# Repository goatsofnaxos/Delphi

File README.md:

# Delphi

Delphi workflow

### Acquisition Prerequisites

The following need to be installed once on a fresh new system in order to bootstrap the Bonsai environment correctly (always check after each download that it has been completed):

 * Windows 10 or greater (Windows 11 after 9/2025)
 * [Visual Studio Code](https://code.visualstudio.com/) (recommended for editing code scripts and git commits)
 * [.NET 8.0 SDK](https://dotnet.microsoft.com/en-us/download/dotnet/8.0)
 * [.NET Framework 4.7.2 Developer Pack](https://dotnet.microsoft.com/download/dotnet-framework/thank-you/net472-developer-pack-offline-installer) (required for intellisense when editing code scripts)
 * [Git for Windows](https://gitforwindows.org/) (recommended for cloning and manipulating this repository)
 * [Visual C++ Redistributable for Visual Studio 2012](https://www.microsoft.com/en-us/download/details.aspx?id=30679) (native dependency for OpenCV)
 * [FTDI D2XX COM Port Driver 2.12.28](https://ftdichip.com/drivers/d2xx-drivers/) (serial port drivers for HARP devices)
   * To download the installer, scroll down, and click *available as a setup executable*.
 * [Spinnaker SDK 1.29.0.5](https://www.flir.co.uk/support/products/spinnaker-sdk/#Downloads) (device drivers for FLIR cameras, sign in required, look in the archived stable versions for 1.29.0.5 64-bit full install)
 * [Github Desktop](https://desktop.github.com/download/) (convenient for testing different PRs)
 * [Python](https://www.python.org/downloads/)

 ### Setting up the Bonsai environment
 To set up a Bonsai environment for running Delphi, use the terminal to clone the repo into a local folder:

 ``` 
 git clone https://github.com/goatsofnaxos/Delphi.git 
 ```

 Now navigate into Delphi/.bonsai and run the `Setup.ps1` script (on Windows right-click > Run with powershell). Once all dependencies have been restored Bonsai can be launched in a local environment from the `.exe` in this folder.

 ### Setting up the Python environment
 A local Python environment is used within the Delphi workflow for certain subprocesses (e.g. robocopy of data). This is separate to the Python environment used for postprocessing and data analysis. To activate this environment after cloning the repo, navigate to Delphi/.python and run the `setup.ps1` script (on Windows right-click > Run with powershell).

 ### Session Settings
 Experiment parameters are based on two data schemas `data-schema` and `rule-schema`. `data-schema` defines global experiment parameters such as animal ID information, logging paths, odor delivery times etc. `rule-schema` defines the experiment state machine with rules for how different states transition to each other. Implementations of these schemas are defined in `.yml` files provided by the user that are then loaded in Bonsai to set up experiment parameters.

 #### Working with data schemas in Visual Studio Code
 To create and edit schema implementations with full autcomplete and hinting, Visual Studio Code requires some extensions to be added:
 * json (ZainChen.json)
 * JSON Schema Validator (tberman.json-schema-validator)
 * YAML (redhat.vscode-yaml)

 #### Creating an experiment parameter file
 To create an experiment parameter file based on the `data-schema`, create a new `.yml` file and add a reference to the `data-schema` at the top of the file:

 ```
 %YAML 1.1
 ---
 # yaml-language-server: $schema=data-schema.json
 ```

The `data-schema` has three main groups of parameters to define: general metadata; camera properties; and line mappings, e.g.:

```
metadata:
  animalId: CK001
  loggingRootPath: C:\Users\user\data\
  chargeTime: 0.2
  minimumPokeTime: 0.1
  maximumPokeTime: 10
  robocopyTimeInterval: 3600
  showHarpLeds: false
  maxVideoLength: 20
  minOdorDelivery: 0.1
  maxOdorDelivery: 8
  switchTime1: 0.035
  switchTime2: 0.025
  useVacuum: true
  *There are more parameters to set now. Refer to "Checklist_HIW3_2024_updated....docx" file in
   Delphi > Design and Operations > Running the experiment

cameraProperties:
  imagingRate: 100
  preEventBufferFrames: 20
  postEventBufferFrames: 20
  bufferInterval: 1

lineMappings:
  odorMap:
    -   {name: "OdorA", line: 5}
    -   {name: "OdorB", line: 6}
    -   {name: "OdorC", line: 7}
  portLine: 0
  vacuumLine: 2
  auxLine: 1
```

#### Creating a rule file
To create a rule file based on the `rule-schema`, create a new `.yml` file and add a reference to the `rule-schema` at the top of the file.

```
%YAML 1.1
---
# yaml-language-server: $schema=rule-schema.json
```

Rule files have two main components:
* The rule alias which defines the human-readable name or description of the rule.
* State transition definitions which define which state to transition to after a given state has completed. The state names given here must match their names in the Bonsai workflow. For example:

```
ruleAlias: Rule1

stateDefinitions:
  -   {name: "OdorA", transitionsTo: "OdorB"}
  -   {name: "OdorB", transitionsTo: "OdorC"}
  -   {name: "OdorC", transitionsTo: "OdorA"}
  -   {name: "DefaultState", transitionsTo: "OdorA"}
```

It is important to always define a DefaultState transition rule, as this is the default fallback in case any states are not present.

### Running an experiment
To run an experiment, run the Bonsai application from the local environment and open DelphiMain.bonsai. Use the property grid to select the desired experiment parameter file and starting rule file. If the rule file is changed while the experiment is running, Bonsai will attempt to find a transition from its current state in the new rule file. If no transition is defined for that state in the new rule, or any of the states no longer exist in the new rule - Bonsai will transition to the default state.

### Data transfer
The main Delphi workflow periodically copies logged data with [Robocopy](https://learn.microsoft.com/en-us/windows-server/administration/windows-commands/robocopy) to a new data location (can be a local or remote destination). The parameters for this transfer are set via the schema .yml:
  - `loggingRootPath`: where data is immediately logged
  - `remoteTransferRootPath`: where data should be transferred
  - `robocopyTimeInterval`: the time interval (in seconds) that Robocopy should be activated.

Note also that exiting the workflow process with the exit trigger key will initiate Robocopy.

### Analysis Prerequisites

The following need to be installed once on a fresh new system in order to analyze data acquired with Delphi:

 * [Visual Studio Code](https://code.visualstudio.com/) (recommended for editing code scripts and git commits)
 * A Conda distribution such as [Miniconda](https://docs.anaconda.com/free/miniconda/index.html)
 * [Python Extension for VS Code](https://marketplace.visualstudio.com/items?itemName=ms-python.python)
   * This extension needs to be made aware of the Conda installation. To do so, navigate to the extension settings. Under the section **Python: Conda Path**, enter the full path to the conda.bat executable. ([more info](https://stackoverflow.com/a/77615160/3312269).)
 * [Jupyter Extension for VS Code](https://marketplace.visualstudio.com/items?itemName=ms-toolsai.jupyter)

#### Create local Environment

 1. Open the Delphi folder in VS Code
 2. `Ctrl+Shift+P` in VS Code > Python: Create Environment
   * Select Conda
   * Select Python 3.11 kernel
 3. Ensure pip is upgraded by typying this into VSCode terminal:
    ```
    pip install --upgrade pip
    ```
 4. From the VSCode terminal run `pip install -r requirements.txt`
 5. Clone aeon_mecha into a separate directory 
    ```
    git clone https://github.com/SainsburyWellcomeCentre/aeon_mecha.git 
    ```
 6. From the VS Code terminal, `cd` into the aeon_mecha directory and run:
    ```
    python -m pip install -e .
    ```
 7. In VS Code open an analysis notebook (.ipynb) and click "Select kernel" > Python Environments
   * Select .conda local environment
 8. Analysis notebooks should now be able to run. If you get an error saying a module can't be found, try restarting the kernel in the notebook editor.

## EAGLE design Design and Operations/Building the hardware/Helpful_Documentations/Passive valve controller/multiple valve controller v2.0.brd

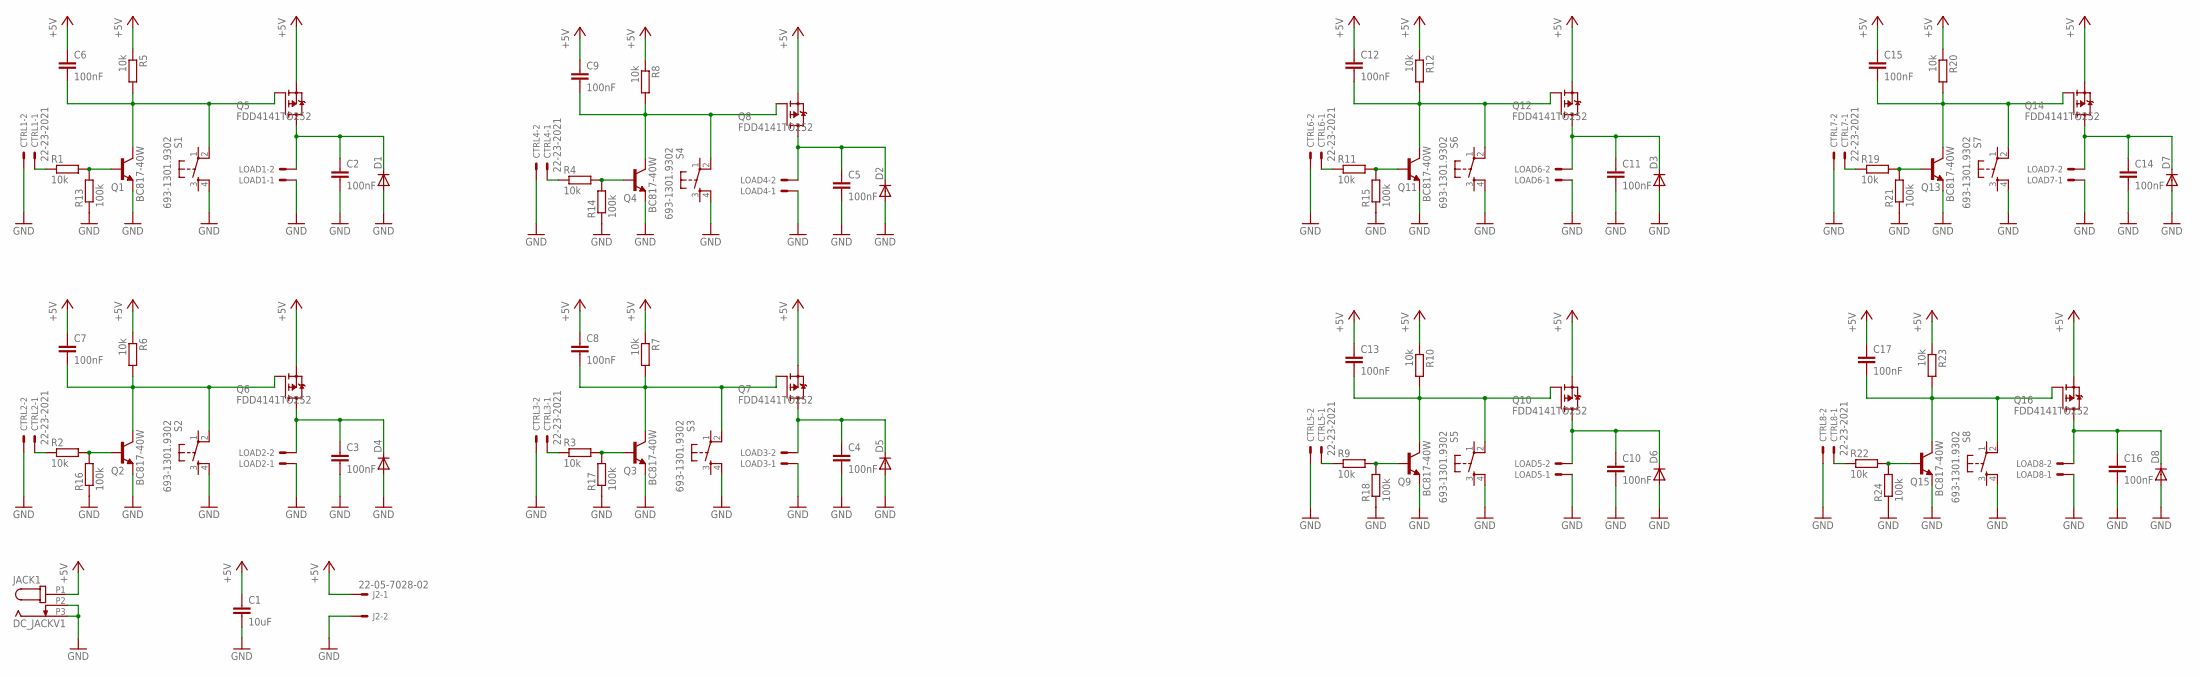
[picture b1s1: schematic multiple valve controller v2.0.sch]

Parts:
C1: 10uF; C1210
C2, C3, C4, C5, C10, C11, C14, C16: 100nF; C1210
C6, C7, C8, C9, C12, C13, C15, C17: 100nF; C0603
CTRL1, CTRL2, CTRL3, CTRL4, CTRL5, CTRL6, CTRL7, CTRL8: 22-23-2021
D1, D2, D3, D4, D5, D6, D7, D8: DIODE-SOD323-R; SOD323-R
J2: 22-05-7028-02; 7395-02
JACK1: DC_JACKV1; DC_POWER_INPUT
LOAD1, LOAD2, LOAD3, LOAD4, LOAD5, LOAD6, LOAD7, LOAD8: 22-23-2021
Q1, Q2, Q3, Q4, Q9, Q11, Q13, Q15: BC817-40W; SOT323-BEC
Q5, Q6, Q7, Q8, Q10, Q12, Q14, Q16: FDD4141TO252; TO252
R1, R2, R3, R4, R9, R11, R19, R22: 10k; R0402
R5, R6, R7, R8, R10, R12, R20, R23: 10k; R0603
R13, R14, R15, R16, R17, R18, R21, R24: 100k; R0402
S1, S2, S3, S4, S5, S6, S7, S8: 693-1301.9302; TACTILE-PTH

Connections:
+5V: C1.1, C6.1, C7.1, C8.1, C9.1, C12.1, C13.1, C15.1, C17.1, J2.1, JACK1.P1 (1), Q5.2 (S), Q6.2 (S), Q7.2 (S), Q8.2 (S), Q10.2 (S), Q12.2 (S), Q14.2 (S), Q16.2 (S), R5.1, R6.1, R7.1, R8.1, R10.1, R12.1, R20.1, R23.1
GND: C1.2, C2.2, C3.2, C4.2, C5.2, C10.2, C11.2, C14.2, C16.2, CTRL1.2, CTRL2.2, CTRL3.2, CTRL4.2, CTRL5.2, CTRL6.2, CTRL7.2, CTRL8.2, D1.A, D2.A, D3.A, D4.A, D5.A, D6.A, D7.A, D8.A, J2.2, JACK1.P2 (2), JACK1.P3 (3), LOAD1.1, LOAD2.1, LOAD3.1, LOAD4.1, LOAD5.1, LOAD6.1, LOAD7.1, LOAD8.1, Q1.E, Q2.E, Q3.E, Q4.E, Q9.E, Q11.E, Q13.E, Q15.E, R13.1, R14.1, R15.1, R16.1, R17.1, R18.1, R21.1, R24.1, S1.4, S2.4, S3.4, S4.4, S5.4, S6.4, S7.4, S8.4
unnamed: CTRL1.1, R1.1
unnamed: C3.1, D4.C, LOAD2.2, Q6.3 (D)
unnamed: C8.2, Q3.C, Q7.1 (G), R7.2, S3.2
unnamed: Q2.B, R2.2, R16.2
unnamed: CTRL2.1, R2.1
unnamed: C4.1, D5.C, LOAD3.2, Q7.3 (D)
unnamed: C13.2, Q9.C, Q10.1 (G), R10.2, S5.2
unnamed: Q3.B, R3.2, R17.2
unnamed: C2.1, D1.C, LOAD1.2, Q5.3 (D)
unnamed: CTRL3.1, R3.1
unnamed: C5.1, D2.C, LOAD4.2, Q8.3 (D)
unnamed: C12.2, Q11.C, Q12.1 (G), R12.2, S6.2
unnamed: Q4.B, R4.2, R14.2
unnamed: CTRL4.1, R4.1
unnamed: C7.2, Q2.C, Q6.1 (G), R6.2, S2.2
unnamed: C9.2, Q4.C, Q8.1 (G), R8.2, S4.2
unnamed: Q1.B, R1.2, R13.2
unnamed: C15.2, Q13.C, Q14.1 (G), R20.2, S7.2
unnamed: C17.2, Q15.C, Q16.1 (G), R23.2, S8.2
unnamed: C10.1, D6.C, LOAD5.2, Q10.3 (D)
unnamed: Q9.B, R9.2, R18.2
unnamed: CTRL5.1, R9.1
unnamed: C11.1, D3.C, LOAD6.2, Q12.3 (D)
unnamed: Q11.B, R11.2, R15.2
unnamed: CTRL6.1, R11.1
unnamed: C6.2, Q1.C, Q5.1 (G), R5.2, S1.2
unnamed: C14.1, D7.C, LOAD7.2, Q14.3 (D)
unnamed: Q13.B, R19.2, R21.2
unnamed: CTRL7.1, R19.1
unnamed: C16.1, D8.C, LOAD8.2, Q16.3 (D)
unnamed: Q15.B, R22.2, R24.2
unnamed: CTRL8.1, R22.1

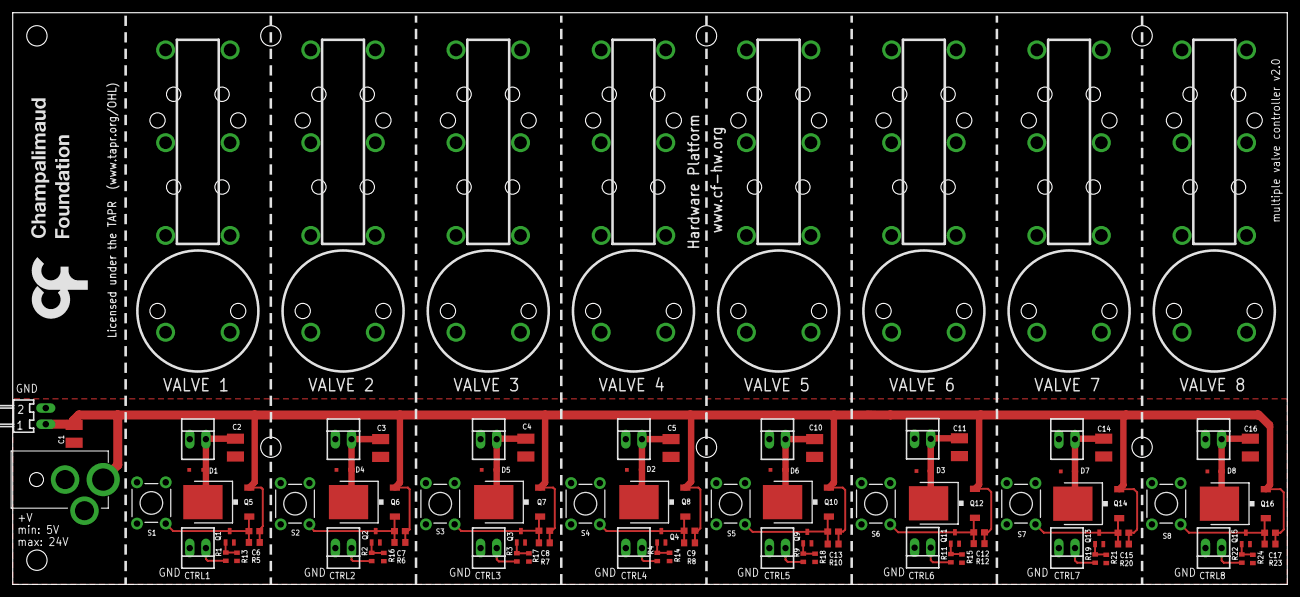
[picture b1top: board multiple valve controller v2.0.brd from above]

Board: 2 copper layers, 200.7 x 90.0 mm, 92 parts (0 on the bottom side), 34 nets.

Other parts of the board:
U$1: LOGO_5

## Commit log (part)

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2026-01-30 Add operator to sequence rule schedule changes
    RuleTimer generates a sequence of rule schedules from a pre-programmed
    list.
    The contents of schedule schema files are loaded into memory and output
    at the specified absolute due time indicated in the schedule.
2026-01-30 Minor cumulative poke count visualization updates
2026-01-30 Implement rule switch time in workflow
2026-02-02 Poke count visualization
2026-02-02 Update rules
2026-02-04 remove bonsai main
2026-02-04 change schemas
2026-02-05 Update generated sgen classes
2026-02-05 Modify property to avoid merge conflict
2026-02-05 Fix operator connection logic after merge conflict resolution
2026-02-06 schemas and rules addedd
2026-02-06 whiterabbit and resolution fixed
2026-02-07 change path
2026-02-07 set up schemas
2026-02-07 schemas changed and 2nd bonsai
2026-02-09 schemas change
2026-02-09 change back to cup
2026-02-10 Additional QC tests
2026-02-12 changed
2026-02-12 fixed rule saving issue
2026-02-12 fixed rules saving issue
2026-02-13 False poke QC
2026-02-13 Ignore changes to .layout and .editor files
2026-02-18 new experiment new schema, remove take node for rule metadata saving
2026-02-20 Aquire from multiple cameras
2026-02-23 Priouette addtions
2026-02-23 Hardware schema updated
2026-02-23 Manual or automated path prefix
2026-02-24 Reinitialization settings
2026-02-26 20260226experiment
2026-02-26 Add manual datetime parameter to hardware schema
2026-03-05 Define key to stop workflow and do final robocopy
    Files may take a while to flush completely to disk so we wait a few
    seconds before triggering robocopy.
2026-03-05 0305experiment
2026-03-06 Multi-camera updates
2026-03-06 Small fixes
2026-03-07 FLIR and Arducam workflows
2026-03-09 Event based poke clips and code clean up
2026-03-12 03122026experiment
2026-03-13 Intermediate result logging
2026-03-13 Updated schema and logging
2026-03-14 Update robocopy paths
2026-03-17 Experiment launcher
2026-03-17 Fix data paths
2026-03-17 ISO formatted session date for mapping
2026-03-18 new experiment for 3/19/2026 exponential and uniform
2026-03-18 Fix file clean up and stopping lifealert
2026-03-20 New delphi controller nuget package that includes odor dwell time register
2026-03-30 Force lifealert process to terminate
2026-03-30 Force lifealert subprocess termination fix
2026-04-03 Odor dwell time setting in workflow
2026-04-08 4/8 experiment
2026-04-15 Arducam test workflow
2026-04-21 update firmware and new experiment
2026-04-22 04222026 experiment
2026-04-24 04242026experiment and white rabbit setting
2026-04-28 Gambet of poke analyses
2026-05-01 NEW BASEMENT SETUPS
2026-05-01 robocopy
2026-05-01 change
2026-05-01 05012026 expt
2026-05-01 Updated poke analysis
2026-05-07 Metadata generation python package
2026-05-07 README formatting
2026-05-11 Median filter video steams
2026-05-11 Multiple output camera triggers
2026-05-12 Fix camera triggering
2026-05-14 Next rule settings configuration fix
2026-05-14 restart
2026-05-15 Spinnaker capture for dragonfly cameras and next rule setting streamlined
2026-05-18 Pirouette only launcher config
2026-05-21 Delphi data processing python package
2026-05-21 Efficient and fast data movement
2026-05-21 Consolidate dataset
2026-05-21 Track env file changes
2026-05-22 Fix subject json parsing and request
2026-05-22 Parse multiple rule setting files for odor names and channel indices
2026-05-26 Acquistion metadata fix and data ingestion for core package
2026-05-26 Add sandbox directories
2026-05-26 0518exp
2026-05-26 0526exp
2026-05-29 Automated data ingestion and dataset curation
2026-05-29 Cleanup package files
2026-06-02 Add datetime column to dataset
2026-06-04 Update data curation and ingestion
2026-06-04 Add env configs
2026-06-04 Add poke metric quantification and visualization
2026-06-04 Add quality control metrics and plots
2026-06-04 CLI integration
2026-06-04 Add documentation support
2026-06-04 Add video processing functions
2026-06-04 Package dependencies and support
2026-06-04 Friendly setup
2026-06-04 Core dataset building script
2026-06-04 Pokeclip processing script
2026-06-04 Dataset snapshot script
2026-06-04 Common and experiment specific snapshot configurations
2026-06-04 Update script for docs
2026-06-04 Full processing pipeline script
2026-06-04 Update docs for scripts
2026-06-04 Deployed 5ec6a64 with MkDocs version: 1.6.1
2026-06-04 Unified MkDocs site for delphi-data and metadata-generator
    Both packages now share a single root site at
    https://goatsofnaxos.github.io/Delphi/ with navigation tabs.
    - Add root mkdocs.yml covering both packages
    - Add root docs/ directory (copies of per-package docs)
    - Add numpy docstrings to all metadata_generator functions
    - Add metadata_generator[docs] optional dependency group
2026-06-04 Deployed fa7c0d9 with MkDocs version: 1.6.1
2026-06-04 Documentation updates
2026-06-04 Deployed 2eb22f3 with MkDocs version: 1.6.1
2026-06-05 Deployed d0fdc98 with MkDocs version: 1.6.1
2026-06-05 Update launcher prompts, recall, cleanup, and docstrings
2026-06-05 Launcher documentation
2026-06-05 Deployed 356745d with MkDocs version: 1.6.1
2026-06-08 Delphi metadata directory organization and processing pipeline updates
2026-06-08 Deployed 4468cd6 with MkDocs version: 1.6.1
2026-06-09 Clean initialization and recovery for state recovery variables
2026-06-09 Deployed 275d473 with MkDocs version: 1.6.1
2026-06-15 Deployed 13f2aa2 with MkDocs version: 1.6.1
2026-06-15 Deployed 66e54bf with MkDocs version: 1.6.1
2026-06-15 Deployed f96bb79 with MkDocs version: 1.6.1
2026-06-15 Deployed 1a59308 with MkDocs version: 1.6.1
2026-06-15 Experiment conductor documentation
2026-06-15 Common visualizations to all experiments
2026-06-15 Deployed 6e2e5c4 with MkDocs version: 1.6.1
2026-06-16 Fix probe model extraction
2026-06-16 Deployed dffbc14 with MkDocs version: 1.6.1
2026-06-16 Enable options for state machine steps of the experiment conductor
2026-06-16 Deployed 366b760 with MkDocs version: 1.6.1
2026-06-17 Data processing gating for pirouette experiments
2026-06-17 Deployed 0d051fa with MkDocs version: 1.6.1
2026-06-17 Fix conductor
2026-06-17 Deployed 3955b54 with MkDocs version: 1.6.1
2026-06-17 Conductor metadata generation
2026-06-17 Deployed 01304de with MkDocs version: 1.6.1
2026-06-17 Deployed 23a3b2d with MkDocs version: 1.6.1
2026-06-17 Deployed e65526f with MkDocs version: 1.6.1
2026-06-18 Unit tests for conductor
2026-06-18 Deployed bfd3580 with MkDocs version: 1.6.1
2026-06-18 Deployed 6426a4f with MkDocs version: 1.6.1
2026-06-18 Deployed 594c4d2 with MkDocs version: 1.6.1
2026-06-19 Deployed 654e9da with MkDocs version: 1.6.1
2026-06-19 Deployed 7b13082 with MkDocs version: 1.6.1
2026-06-19 Deployed b37ebfd with MkDocs version: 1.6.1
2026-06-22 Deployed 3419cfd with MkDocs version: 1.6.1
2026-06-22 Deployed d5f8b17 with MkDocs version: 1.6.1
2026-06-22 Deployed feb1af3 with MkDocs version: 1.6.1
2026-06-22 Deployed 67d6a9f with MkDocs version: 1.6.1
2026-06-22 Deployed d0965c7 with MkDocs version: 1.6.1
2026-06-22 Deployed 10d7786 with MkDocs version: 1.6.1

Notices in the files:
Design and Operations/Building the hardware/Helpful_Documentations/Passive valve controller/multiple valve controller v2.0.brd:
Licensed under the TAPR Open
Hardware License (www.tapr.org/OHL)
Copyright 2020 Hardware Platform
Licensed under the TAPR  (www.tapr.org/OHL)
parts and their libraries:
SparkFun-Electromechanical: Licensing: CC v3.0 Share-Alike You are welcome to use this library for commercial purposes.
